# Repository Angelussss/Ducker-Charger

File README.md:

<div align="center">

# ⚡ Ducker-Charger

**A fully custom, open-source smart power bank, designed from scratch.**

*4S3P Li-Ion pack · bidirectional USB-PD · bench-supply output · TFT telemetry UI*

<table>
  <tr>
    <td align="center"></td>
    <td align="center"></td>
  </tr>
  <tr>
    <td align="center"><em>Enclosure (prototype 3, lid off)</em></td>
    <td align="center"><em>Live telemetry UI</em></td>
  </tr>
</table>

</div>

> [!WARNING]
> **Work in progress: the design is not yet validated.** This project involves
> Li-Ion batteries, which can overheat, catch fire, or explode if mishandled.
> Take any information here at your own risk and read the safety note below.

## 🌟 Highlights

* **115 Wh**: 12× 18650 cells (Sony Murata VTC5, 4S3P), 14.4 V nominal / 16.8 V max
* **2× USB-C PD**: primary port is bidirectional (charges the pack *and* powers loads)
* **2× USB-A**: fixed 5 V, individually switchable, current-monitored
* **Lab output**: banana-jack rail that behaves like a bench power supply
* **Hardware-autonomous BMS**: BQ77915 protection works even if all firmware fails
* **STM32F401 supervisor**: power-state FSM, charge management, TFT + rotary-encoder UI
* **On-device gauge calibration**: guided 9-step wizard on the display; a multimeter is the only tool needed (no bqStudio / EV2400)
* **Develop without hardware**: full-PCB emulator, desktop UI simulator, host-side unit tests

## ⚠️ Safety & Disclaimer

* **I assume no liability** for any damage to property, people, or components resulting from the construction or use of this project.
* Always double-check polarity before connecting the batteries.
* Do not attempt to assemble this circuit if you are not experienced in handling lithium batteries.

## 🛠️ Requirements

**Hardware**
* Assembled mainboard + Sensing-Board (`PCB/`)
* 12× 18650 Li-Ion cells, 4S3P (e.g. Sony/Murata VTC5)
* ST-Link V2 (or compatible SWD probe) to flash the STM32F401RBT6
* A USB-PD charger for the primary port, plus USB-C/USB-A cables to exercise the outputs

**Software**
* `arm-none-eabi-gcc`: the firmware builds via the CubeMX-generated `Makefile` in `firmware/cubeMX/`, no IDE required
* `st-flash` (`stlink-tools`) or STM32CubeProgrammer, to flash over SWD
* `gcc` + `SDL2`: only needed for `firmware/emulator/` and `firmware/interface-tester/` (no hardware required to run these)
* Optional: STM32CubeIDE / STM32CubeMX, only to regenerate peripheral init code from `cubeMX.ioc`

## 🧩 Architecture

Distributed design: cell safety, power conversion, PD negotiation and gauging
each live in a dedicated IC; the STM32 supervises, aggregates telemetry and
drives the UI. Block diagram in [`PCB/README.md`](PCB/README.md).

<details>
<summary><strong>Full IC breakdown (10 subsystems)</strong></summary>
<br>

| Subsystem | Part | Role |
|-----------|------|------|
| Safety / Protection | TI **BQ77915** + N-ch MOSFETs | Autonomous, software-independent cell OV/UV/SC/OC cutoff (4S, always-on) |
| Charger | TI **BQ25713** | Buck-boost NVDC battery charger (driven by the TPS25750 on a private I²C bus) |
| Main USB-C PD | TI **TPS25750** | Primary PD port controller; patch bundle streamed by the MCU at every boot |
| Aux USB-C PD | Infineon **CYPD3175** (CCG3PA) | Secondary PD port negotiation (replaced the EOL STUSB4710) |
| Aux programmable rail | ST **STPD01** | I²C-programmable supply for the secondary USB-C / lab output |
| Fuel gauge | TI **BQ34Z100-R2** | Impedance Track™ State-of-Charge / Time-to-Empty |
| Telemetry | TI **INA3221** | 3-channel voltage/current monitoring |
| Step-down | TI **TPS54302 / TPS54202** | Auxiliary rails |
| ESD / I²C isolation | **USBLC6**, **ISO1540** | Port ESD protection, isolated I²C to the battery-referenced gauge |
| Host | **STM32F401RBT6** | I²C master, power-state FSM, thermal manager, HMI / supervisor |

</details>

## 📂 Repository

| Path | Contents |
| --- | --- |
| [`PCB/`](PCB/README.md) | KiCad projects: main board + cell sensing board |
| [`firmware/`](firmware/) | STM32 firmware, PD controller configs, emulator, UI simulator, tests |
| [`docs/`](docs/README.md) | Documentation, start here |
| [`powerbank_enclosure/`](powerbank_enclosure/) | 3D-printable enclosure (F3D, STEP, STL, renders) |

<details>
<summary><strong>Full tree</strong></summary>

```text
Ducker-Charger/
├── PCB/
│   ├── Ducker-Charger/         # Main charger board (schematics, layout, datasheets)
│   └── Sensing-Board/          # Cell sensing board
├── firmware/
│   ├── cubeMX/                 # STM32F401 firmware (FSM, charge mgmt, UI, drivers)
│   ├── TPS25750/               # Primary PD controller config (JSON project + .bin)
│   ├── CYPD3175/               # Secondary PD controller firmware (hex, patches, LED driver)
│   ├── emulator/               # Full-PCB emulator: real firmware vs IC models (SDL)
│   ├── interface-tester/       # Desktop UI simulator (SDL)
│   └── tests/                  # Host-side unit tests (FSM, charge, HPI, math)
├── powerbank_enclosure/        # 3D-printable enclosure (F3D, STEP, STL, renders)
└── docs/
    ├── hardware/               # Power architecture, pin map / BSP reference
    ├── firmware/               # Architecture, FSM, charge mgmt, boot, UI
    └── assets/                 # UI demo gif
```

</details>

## 📖 Documentation

Start from **[`docs/README.md`](docs/README.md)**: full system overview and a
walkthrough of how the firmware works, with links to:

* [Hardware architecture](docs/hardware/Hardware_Architecture.md) · [pin-level BSP reference](docs/hardware/BSP_reference.md)
* [Firmware architecture](docs/firmware/Firmware_Architecture.md) · [power-state FSM](docs/firmware/FSM.md) · [charge management](docs/firmware/Charge_Management.md)
* [Boot & IC provisioning](docs/firmware/Boot_and_Provisioning.md) · [gauge calibration wizard](docs/firmware/Gauge_Calibration.md) · [UI / display reference](docs/firmware/UI_and_Display.md)
* [KiCad projects & block diagram](PCB/README.md)

## 🎮 User Guide

Boots to **MAIN** (battery %, voltage/current, live current graph). Rotate the
encoder to cycle **MAIN → DETAILS → GRAPH → PORTS → STATS**; press to open
**SETTINGS** (per-port toggles, Lab output voltage/current, USB-C2 output
ceiling, lock-all, brightness/auto-sleep, gauge calibration wizard, shutdown).
A long press (or SETTINGS → Shutdown) puts the device into deep sleep; a
short press wakes it back up if a charger is attached. Fault conditions open a
dedicated FAULT screen automatically, naming the cause.

Full screen-by-screen reference: [`docs/firmware/UI_and_Display.md`](docs/firmware/UI_and_Display.md).

## 🎥 Presentation & Demo

* 📊 Slides: [Google Slides](https://docs.google.com/presentation/d/1OwDXiBUUQ08QPd7Jknc45msrt9zxNyJMcGTFnEZxmk4/edit?usp=sharing)
* 🎬 YouTube walkthrough: [youtu.be/msm0JCK7GhI](https://youtu.be/msm0JCK7GhI)

## 👥 Team & Contributions

The project is split by layer, one owner per layer end-to-end (design, implementation, docs, tests):

| Member | Layer owned |
|---|---|
| Angelo Perotti | Hardware (PCB/KiCad), CubeMX project bring-up, boot & IC provisioning |
| Francesco Brunelli | Charge management: sensors, actuators, fault detection |
| Michelangelo Calia | Power-state FSM & fault handling |
| Maya | Display/UI stack: driver, widgets, screens, navigation |

## 🤝 Contributing

Issues, suggestions, and pull requests are momentarily suspended, as this is a university course project.

## 📜 License

Released under the [Creative Commons Attribution-NonCommercial 4.0 Internationalç
License (CC BY-NC 4.0)](LICENSE). © 2026 Angelo Perotti.

You are free to use, modify, and build upon this work for **non-commercial**
purposes, as long as you **credit the author**. See [NOTICE](NOTICE) for
attribution details.

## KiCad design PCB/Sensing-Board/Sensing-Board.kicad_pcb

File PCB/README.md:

# PCB: KiCad Projects

Two KiCad projects make up the Ducker-Charger hardware:

| Project | Contents |
| --- | --- |
| `Ducker-Charger/` | Main charger board: schematics, PCB layout, production files |
| `Sensing-Board/` | Cell sensing board (tap connections from the 4S pack to the BMS) |

## Main board schematic structure

| Sheet | File | Contents |
| --- | --- | --- |
| Root | `Ducker-Charger.kicad_sch` | Top level, sheet interconnections |
| High power | `high_pow.kicad_sch` | TPS25750 (primary USB-C PD), BQ25713 buck-boost charger, VBUS power path |
| Low power | `low_pow.kicad_sch` | CYPD3175 (secondary USB-C PD), STPD01 programmable rail, USB-A load switches, INA3221 sensing, lab-output switching |
| Logic | `Logic.kicad_sch` | STM32F401RBT6, display/encoder interface, logic supply |
| BMS | `BMS.kicad_sch` | BQ77915 protection, BQ34Z100-R2 fuel gauge, ISO1540 I2C isolator, protection FETs |

> The secondary PD controller is the Infineon **CYPD3175**: it replaced the
> ST **STUSB4710** (EOL).

Component datasheets and technical reference manuals used during the design are
collected in [`Ducker-Charger/docs/`](Ducker-Charger/docs/).

## System block diagram

```mermaid
flowchart TB
    subgraph BMS["BMS (always-on hardware safety)"]
        PACK["4S3P Sony VTC5<br/>14.4V nom / 16.8V max"]
        BQ77915["BQ77915 protector<br/>+ N-ch FETs (low-side)"]
        GAUGE["BQ34Z100-R2 fuel gauge<br/>(battery-referenced)"]
        PACK --> BQ77915
        PACK -.->|sense| GAUGE
    end

    subgraph HP["High-power stage"]
        TPS["TPS25750<br/>primary USB-C PD"]
        BQ25713["BQ25713<br/>buck-boost NVDC charger"]
        USBC1(("USB-C1<br/>bidirectional PD"))
        USBC1 <--> TPS
        TPS <-->|private I2C_EX| BQ25713
    end

    subgraph LP["Low-power / aux stage"]
        CYPD["CYPD3175<br/>secondary USB-C PD"]
        STPD01["STPD01<br/>programmable rail"]
        USBC2(("USB-C2<br/>source-only"))
        USBA(("2x USB-A<br/>5V"))
        LAB(("Lab output"))
        INA["INA3221<br/>current monitor"]
        CYPD <--> USBC2
        STPD01 --> USBC2
        STPD01 --> LAB
        INA --- USBA
    end

    subgraph LOGIC["Logic"]
        MCU["STM32F401RBT6"]
        DISP["ILI9341 TFT (SPI1)"]
        ENC["Rotary encoder (TIM3)"]
        MCU --> DISP
        ENC --> MCU
    end

    BQ77915 -->|+BATT| BQ25713
    BQ25713 -->|VSYS| LP
    BQ25713 -->|VSYS| LOGIC

    MCU <-->|"I2C3 (PD bus)"| TPS
    MCU <-->|"I2C1 (system bus, HPI)"| CYPD
    MCU <-->|I2C1| STPD01
    MCU <-->|I2C1| INA
    MCU <-->|"I2C1 via ISO1540"| GAUGE
```

Bus-level detail (pins, addresses):
[`docs/hardware/BSP_reference.md`](../docs/hardware/BSP_reference.md).

## Production

`*/production/` holds the fabrication outputs (gerber zip + IPC netlist)
generated with the JLCPCB fabrication toolkit. Regenerate after any layout
change; do not hand-edit.

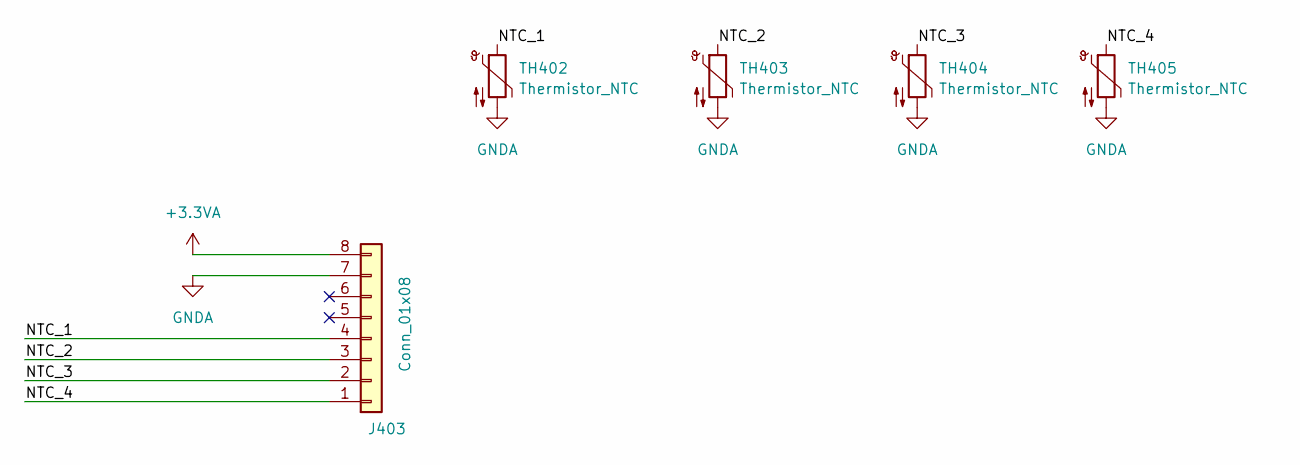
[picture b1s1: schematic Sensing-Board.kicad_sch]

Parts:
J403: Conn_01x08; Molex_200528-0080_1x08-1MP_P1.00mm_Horizontal
TH402, TH403, TH404, TH405: Thermistor_NTC; R_0603_1608Metric

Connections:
+3.3VA: J403.8
/NTC_1: J403.4, TH402.1
/NTC_2: J403.3, TH403.1
/NTC_3: J403.2, TH404.1
/NTC_4: J403.1, TH405.1
GNDA: J403.7, TH402.2, TH403.2, TH404.2, TH405.2

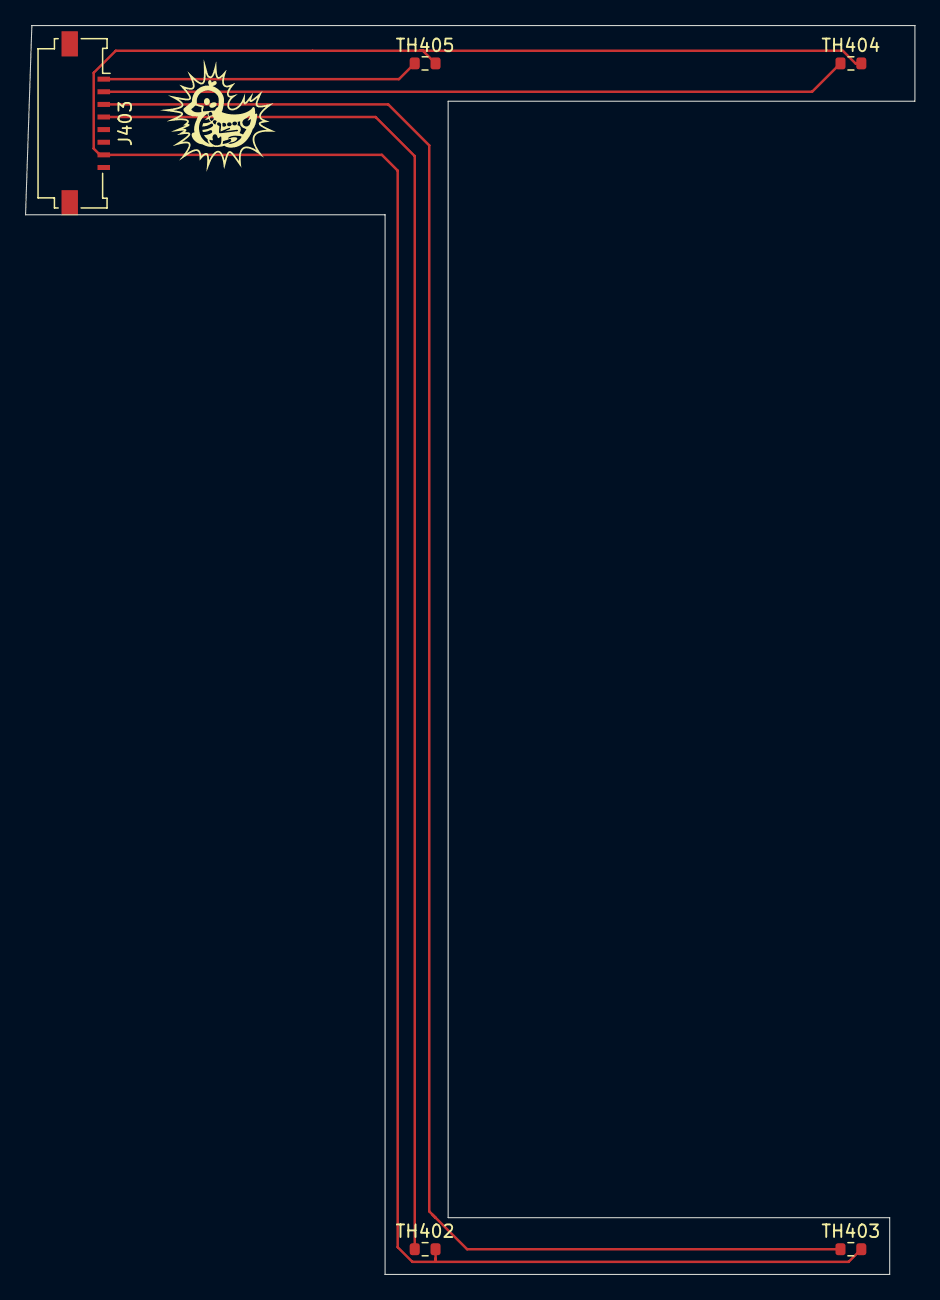
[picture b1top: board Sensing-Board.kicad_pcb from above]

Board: 2 copper layers, 70.5 x 99.0 mm, 6 parts (1 on the bottom side), 5 nets.

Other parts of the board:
kibuzzard-6A3C49BF: G***; kibuzzard-6A3C49BF

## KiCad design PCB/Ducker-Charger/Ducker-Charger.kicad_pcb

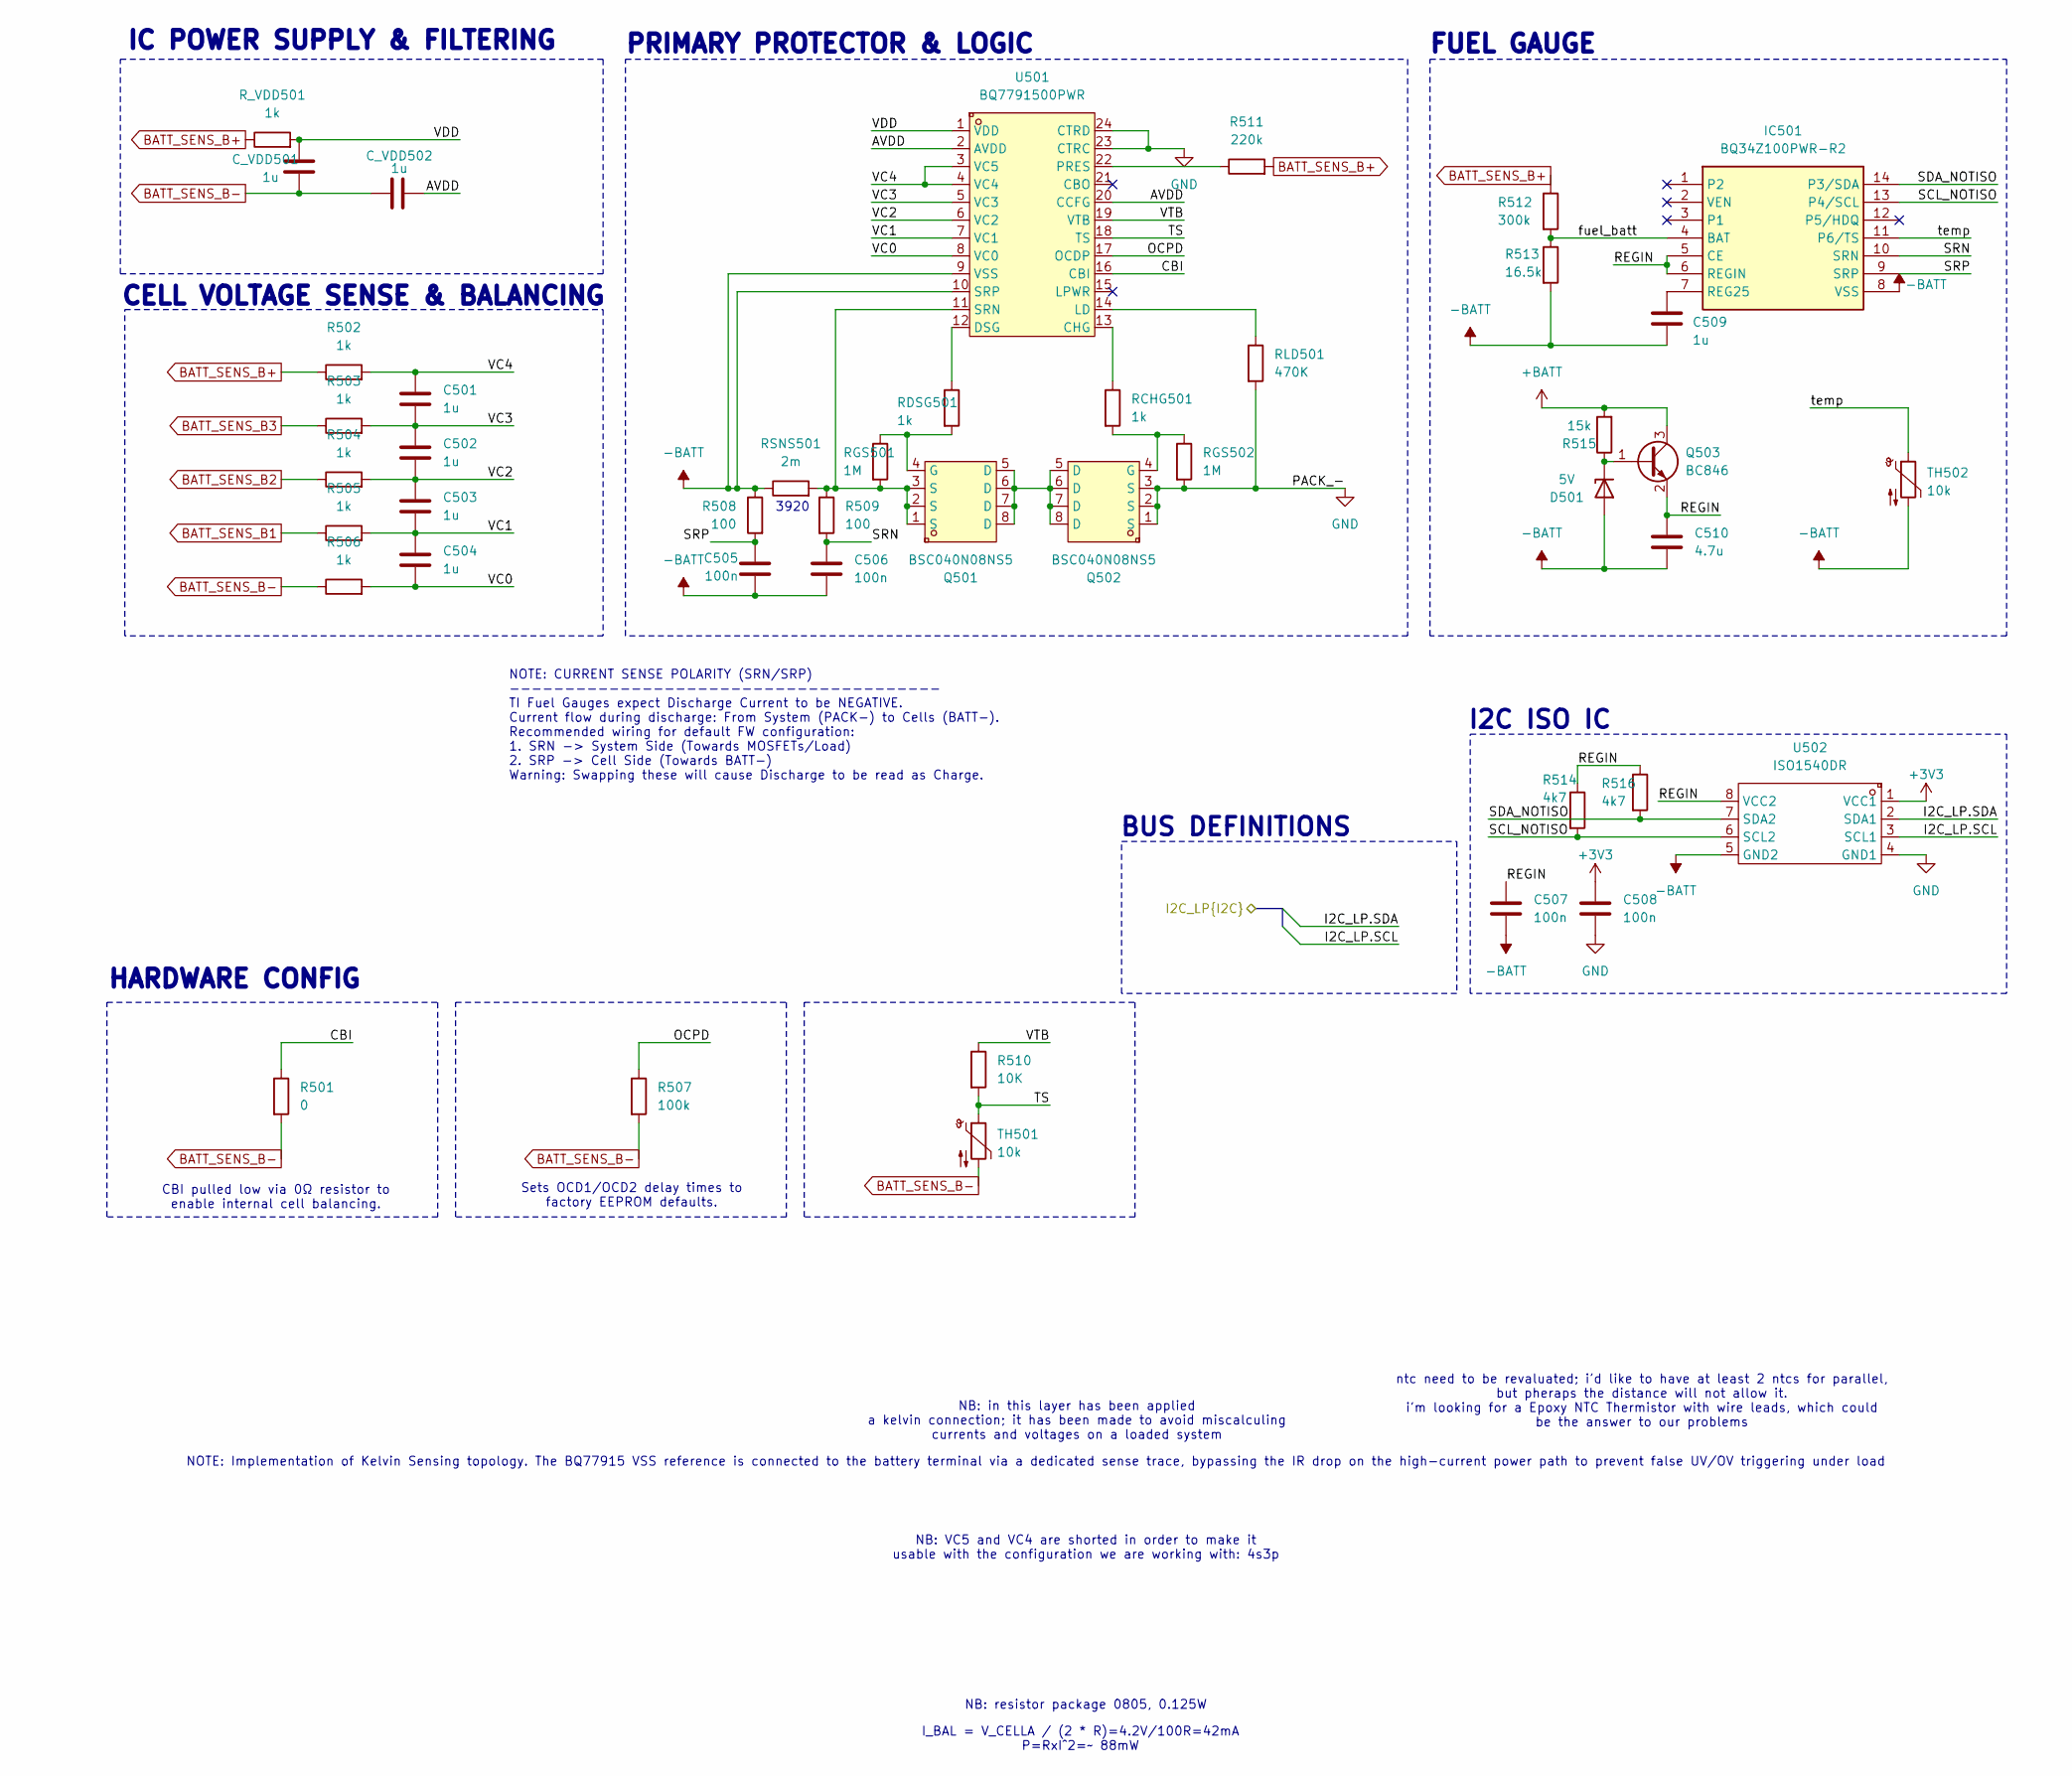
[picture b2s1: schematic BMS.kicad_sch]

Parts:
C501, C502, C503, C504, C509: 1u; C_0805_2012Metric
C505, C506, C507, C508: 100n; C_0603_1608Metric
C510: 4.7u; C_0805_2012Metric
C_VDD501, C_VDD502: 1u; C_0805_2012Metric
D501: 5V; D_SOD-123
IC501: BQ34Z100PWR-R2; SOP65P640X120-14N; Mouser Part Number 595-BQ34Z100PWR-R2
Q501, Q502: BSC040N08NS5; PG-TDSON-8_L5.9-W5.1-P1.27-LS6.2-BL; LCSC Part C534333
Q503: BC846; SOT-23
R501: 0; R_0603_1608Metric
R502, R503, R504, R505, R506: 1k; R_0603_1608Metric
R507: 100k; R_0603_1608Metric
R508, R509: 100; R_0603_1608Metric
R510: 10K; R_0603_1608Metric
R511: 220k; R_0603_1608Metric
R512: 300k; R_0603_1608Metric
R513: 16.5k; R_0603_1608Metric
R514, R516: 4k7; R_0603_1608Metric
R515: 15k; R_0603_1608Metric
RCHG501: 1k; R_0603_1608Metric
RDSG501: 1k; R_0603_1608Metric
RGS501, RGS502: 1M; R_0603_1608Metric
RLD501: 470K; R_0603_1608Metric
RSNS501: 2m; R3920; lcsc name Milliohm HoJLR2512-3W-5mR-1%
R_VDD501: 1k; R_0603_1608Metric
TH501, TH502: 10k; R_0603_1608Metric
U501: BQ7791500PWR; TSSOP-24_L7.8-W4.4-P0.65-LS6.4-BL; LCSC Part C2876946
U502: ISO1540DR; SOIC-8_L4.9-W3.9-P1.27-LS6.0-BL; LCSC Part C179739

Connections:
+3V3: C508.1, U502.1 (VCC1); also elsewhere on the board
+BATT: Q503.3 (C), R515.2; also elsewhere on the board
-BATT: C505.2, C506.2, C507.2, C509.2, C510.2, D501.2 (A), IC501.8 (VSS), R508.1, R513.2, RSNS501.1, TH502.2, U501.9 (VSS), U501.10 (SRP), U502.5 (GND2); also elsewhere on the board
/BMS/AVDD: C_VDD502.2, U501.2 (AVDD), U501.20 (CCFG)
/BMS/CBI: R501.1, U501.16 (CBI)
/BMS/I2C_LP.SCL: U502.3 (SCL1); also elsewhere on the board
/BMS/I2C_LP.SDA: U502.2 (SDA1); also elsewhere on the board
/BMS/OCPD: R507.1, U501.17 (OCDP)
/BMS/REGIN: C507.1, C510.1, IC501.5 (CE), IC501.6 (REGIN), Q503.2 (E), R514.1, R516.1, U502.8 (VCC2)
/BMS/SCL_NOTISO: IC501.13 (P4/SCL), R514.2, U502.6 (SCL2)
/BMS/SDA_NOTISO: IC501.14 (P3/SDA), R516.2, U502.7 (SDA2)
/BMS/SRN: C506.1, IC501.10 (SRN), R509.2
/BMS/SRP: C505.1, IC501.9 (SRP), R508.2
/BMS/TS: R510.2, TH501.1, U501.18 (TS)
/BMS/VC0: C504.2, R506.2, U501.8 (VC0)
/BMS/VC1: C503.2, C504.1, R505.2, U501.7 (VC1)
/BMS/VC2: C502.2, C503.1, R504.2, U501.6 (VC2)
/BMS/VC3: C501.2, C502.1, R503.2, U501.5 (VC3)
/BMS/VC4: C501.1, R502.2, U501.3 (VC5), U501.4 (VC4)
/BMS/VDD: C_VDD501.1, R_VDD501.2, U501.1 (VDD)
/BMS/VTB: R510.1, U501.19 (VTB)
/BMS/fuel_batt: IC501.4 (BAT), R512.2, R513.1
/BMS/temp: IC501.11 (P6/TS), TH502.1
BATT_SENS_B1: R505.1; also elsewhere on the board
BATT_SENS_B2: R504.1; also elsewhere on the board
BATT_SENS_B3: R503.1; also elsewhere on the board
BATT_SENS_B+: R502.1, R511.2, R512.1, R_VDD501.1; also elsewhere on the board
BATT_SENS_B-: C_VDD501.2, C_VDD502.1, R501.2, R506.1, R507.2, TH501.2; also elsewhere on the board
GND: C508.2, Q502.1 (S), Q502.2 (S), Q502.3 (S), RGS502.2, RLD501.2, U501.23 (CTRC), U501.24 (CTRD), U502.4 (GND1); also elsewhere on the board
unnamed: D501.1 (K), Q503.1 (B), R515.1
unnamed: C509.1, IC501.7 (REG25)
unnamed: Q501.5 (D), Q501.6 (D), Q501.7 (D), Q501.8 (D), Q502.5 (D), Q502.6 (D), Q502.7 (D), Q502.8 (D)
unnamed: Q501.4 (G), RDSG501.2, RGS501.1
unnamed: Q502.4 (G), RCHG501.2, RGS502.1
unnamed: RCHG501.1, U501.13 (CHG)
unnamed: RDSG501.1, U501.12 (DSG)
unnamed: RLD501.1, U501.14 (LD)
unnamed: R511.1, U501.22 (PRES)
unnamed: Q501.1 (S), Q501.2 (S), Q501.3 (S), R509.1, RGS501.2, RSNS501.2, U501.11 (SRN)

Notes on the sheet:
NB: resistor package 0805, 0.125W
I2C ISO IC
NOTE: Implementation of Kelvin Sensing topology. The BQ77915 VSS reference is connected to the battery terminal via a dedicated sense trace, bypassing the IR drop on the high-current power path to prevent false UV/OV triggering under load
FUEL GAUGE
I_BAL = V_CELLA / (2 * R)=4.2V/100R=42mA P=RxI^2=~ 88mW
NOTE: CURRENT SENSE POLARITY (SRN/SRP) --------------------------------------- TI Fuel Gauges expect Discharge Current to be NEGATIVE. Current flow during discharge: From System (PACK-) to Cells (BATT-). Recommended wiring for default FW configuration: 1. SRN -> System Side (Towards MOSFETs/Load) 2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
IC POWER SUPPLY & FILTERING
ntc need to be revaluated; i'd like to have at least 2 ntcs for parallel, but pheraps the distance will not allow it. i'm looking for a Epoxy NTC Thermistor with wire leads, which could be the answer to our problems
NB: in this layer has been applied a kelvin connection; it has been made to avoid miscalculing currents and voltages on a loaded system
Sets OCD1/OCD2 delay times to factory EEPROM defaults.
HARDWARE CONFIG
CELL VOLTAGE SENSE & BALANCING
BUS DEFINITIONS
NB: VC5 and VC4 are shorted in order to make it usable with the configuration we are working with: 4s3p
3920
CBI pulled low via 0Ω resistor to enable internal cell balancing.
PRIMARY PROTECTOR & LOGIC

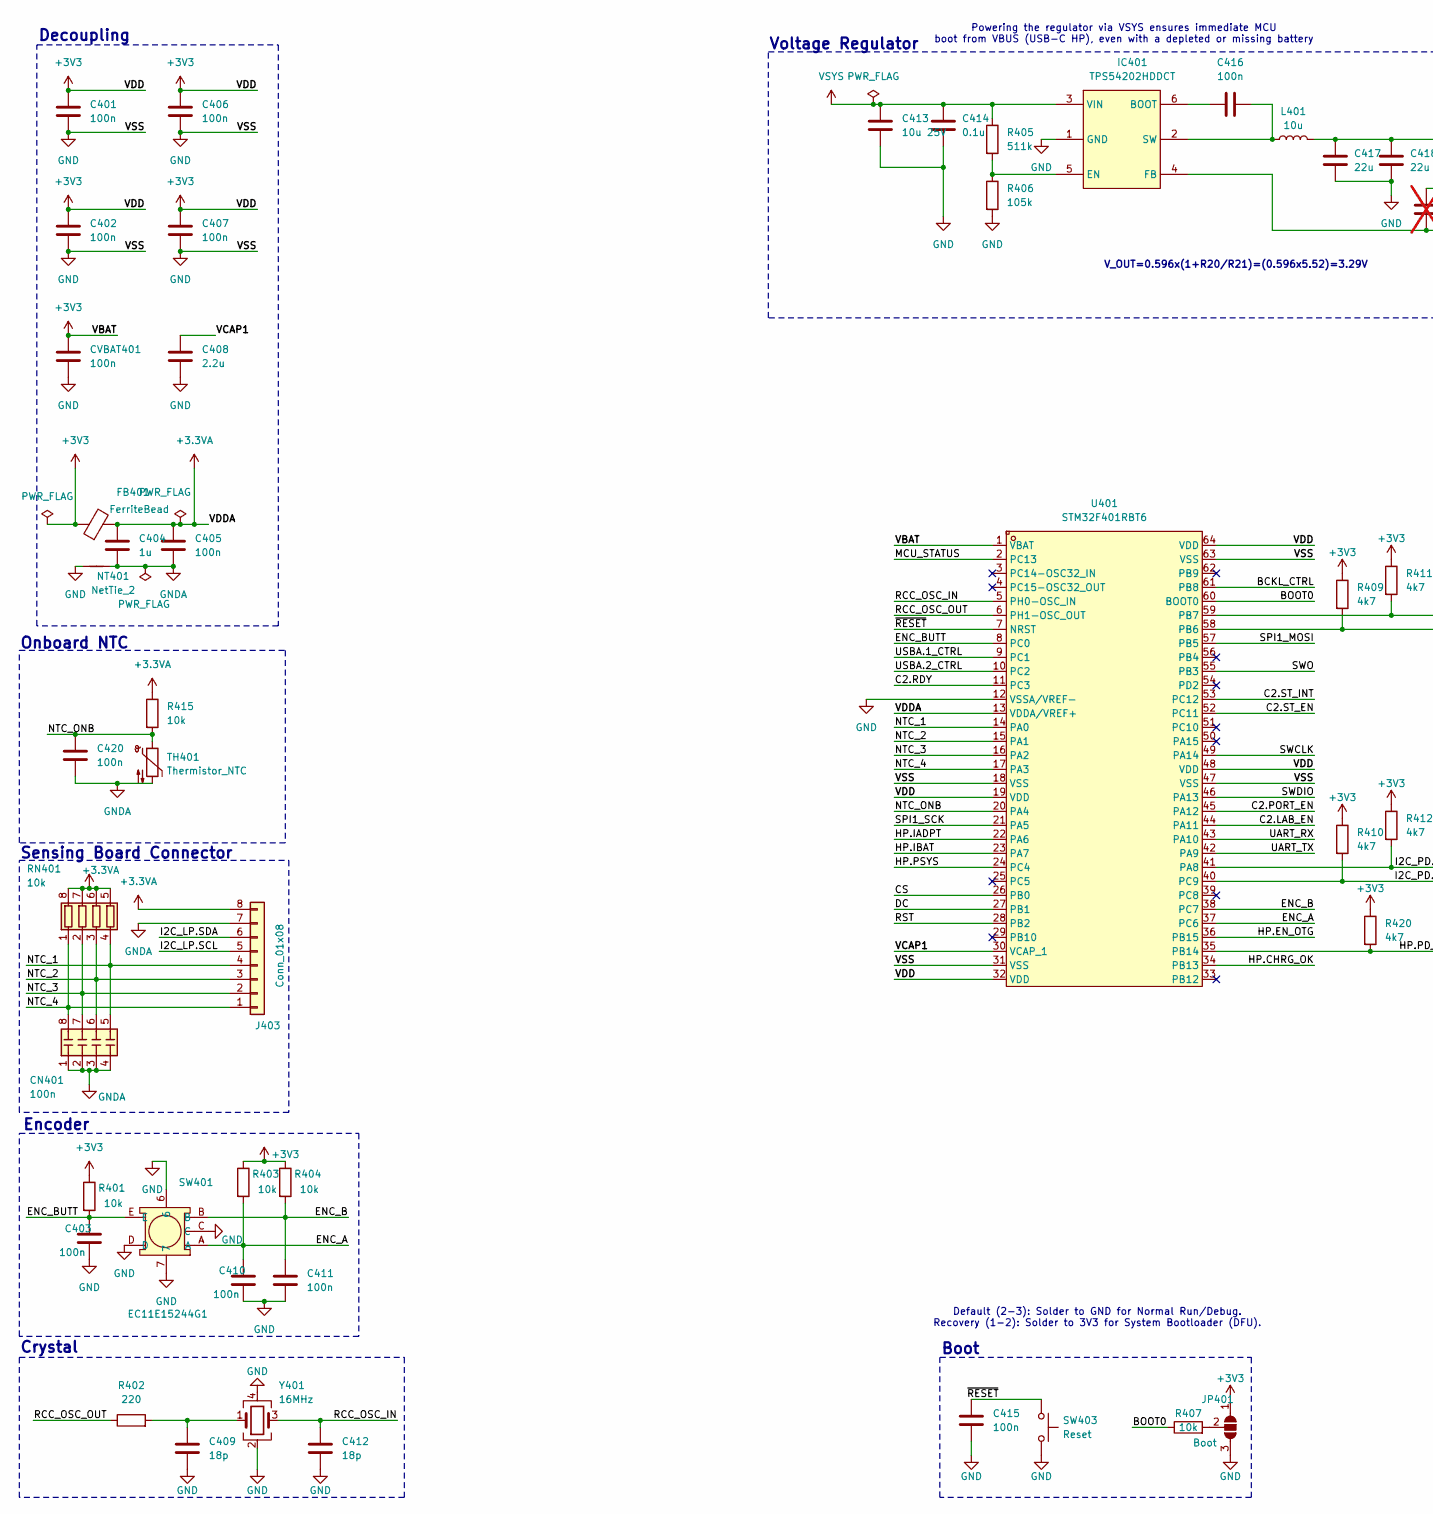
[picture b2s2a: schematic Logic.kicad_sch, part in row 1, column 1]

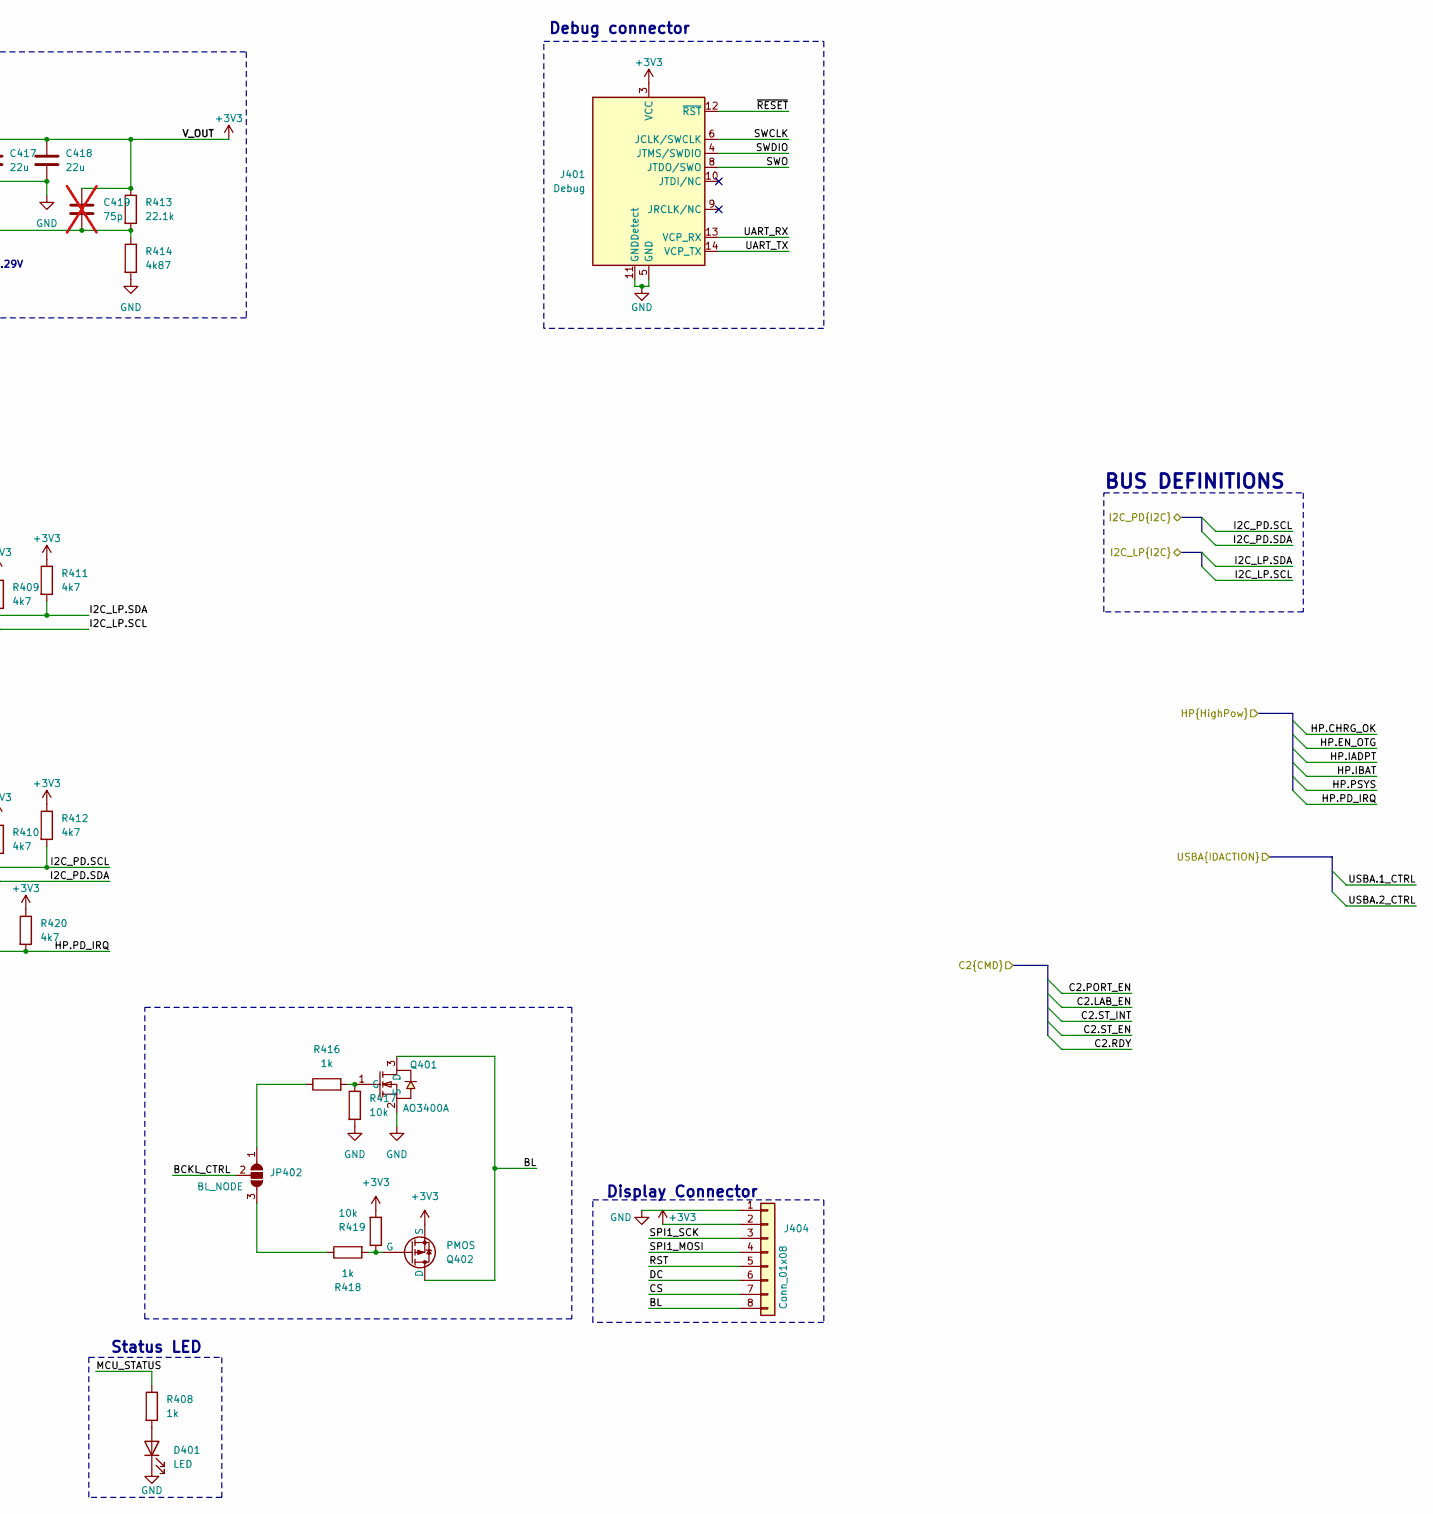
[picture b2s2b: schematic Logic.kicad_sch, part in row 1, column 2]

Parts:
C401, C402, C403, C405, C406, C407, C410, C411, C415, C420: 100n; C_0603_1608Metric
C404: 1u; C_0805_2012Metric
C408: 2.2u; C_0805_2012Metric
C409, C412: 18p; C_0603_1608Metric
C413: 10u 25V; C_1206_3216Metric
C414: 0.1u; C_0805_2012Metric
C416: 100n; C_0805_2012Metric
C417, C418: 22u; C_0805_2012Metric
C419: 75p; C_0805_2012Metric; not fitted
CN401: 100n; R_Array_Concave_4x0603
CVBAT401: 100n; R_0603_1608Metric
D401: LED; LED_0603_1608Metric
FB401: FerriteBead; L_0603_1608Metric
IC401: TPS54202HDDCT; SOT95P280X110-6N; Mouser Part Number 595-TPS54202HDDCT
J401: Debug; SAMTEC_FTSH-107-01-L-DV-K-TR
J403: Conn_01x08; Molex_200528-0080_1x08-1MP_P1.00mm_Horizontal
J404: Conn_01x08; JST_EH_B8B-EH-A_1x08_P2.50mm_Vertical
JP401: Boot; SolderJumper-3_P1.3mm_Open_RoundedPad1.0x1.5mm
JP402: BL_NODE; SolderJumper-3_P1.3mm_Open_RoundedPad1.0x1.5mm
L401: 10u; L_6.3x6.3_H3
NT401: NetTie_2; NetTie-2_SMD_Pad0.5mm
Q401: AO3400A; SOT-23-3_L2.9-W1.3-P1.90-LS2.4-BR; LCSC Part C20917
Q402: PMOS; SOT-23-3_L2.9-W1.3-P1.90-LS2.4-BR
R401, R403, R404, R407, R415, R417, R419: 10k; R_0603_1608Metric
R402: 220; R_0603_1608Metric
R405: 511k; R_0603_1608Metric
R406: 105k; R_0603_1608Metric
R408, R416, R418: 1k; R_0603_1608Metric
R409, R410, R411, R412, R420: 4k7; R_0603_1608Metric
R413: 22.1k; R_0603_1608Metric
R414: 4k87; R_0603_1608Metric
RN401: 10k; R_Array_Convex_4x0603
SW401: EC11E15244G1; SW-TH_EC11E15244G1; LCSC Part C370970
SW403: Reset; SW_SPST_FSMSM
TH401: Thermistor_NTC; R_0603_1608Metric
U401: STM32F401RBT6; LQFP-64_L10.0-W10.0-P0.50-LS12.0-BL; LCSC Part C75278
Y401: 16MHz; Crystal_SMD_EuroQuartz_MT-4Pin_3.2x2.5mm

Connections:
+3.3VA: C404.1, C405.1, FB401.2, J403.8, R415.1, RN401.5 (R4.2), RN401.6 (R3.2), RN401.7 (R2.2), RN401.8 (R1.2), U401.13 (VDDA/VREF+)
+3V3: C401.1, C402.1, C406.1, C407.1, C417.1, C418.1, C419.2, CVBAT401.1, FB401.1, J401.3 (VCC), J404.2, JP401.1 (A), L401.2, Q402.3 (S), R401.1, R403.1, R404.1, R409.1, R410.1, R411.1, R412.1, R413.1, R419.2, R420.1, U401.1 (VBAT), U401.19 (VDD), U401.32 (VDD), U401.48 (VDD), U401.64 (VDD); also elsewhere on the board
/BMS/I2C_LP.SCL: J403.5, R409.2, U401.58 (PB6); also elsewhere on the board
/BMS/I2C_LP.SDA: J403.6, R411.2, U401.59 (PB7); also elsewhere on the board
/High_pow/HP.CHRG_OK: U401.34 (PB13); also elsewhere on the board
/High_pow/HP.EN_OTG: U401.36 (PB15); also elsewhere on the board
/High_pow/HP.IADPT: U401.22 (PA6); also elsewhere on the board
/High_pow/HP.IBAT: U401.23 (PA7); also elsewhere on the board
/High_pow/HP.PD_IRQ: R420.2, U401.35 (PB14); also elsewhere on the board
/High_pow/HP.PSYS: U401.24 (PC4); also elsewhere on the board
/High_pow/I2C_PD.SCL: R412.2, U401.41 (PA8); also elsewhere on the board
/High_pow/I2C_PD.SDA: R410.2, U401.40 (PC9); also elsewhere on the board
/Logic/BCKL_CTRL: JP402.2 (C), U401.61 (PB8)
/Logic/BL: J404.8, Q401.3 (D), Q402.1 (D)
/Logic/BOOT0: R407.1, U401.60 (BOOT0)
/Logic/C2.LAB_EN: U401.44 (PA11); also elsewhere on the board
/Logic/C2.PORT_EN: U401.45 (PA12); also elsewhere on the board
/Logic/C2.RDY: U401.11 (PC3); also elsewhere on the board
/Logic/C2.ST_EN: U401.52 (PC11); also elsewhere on the board
/Logic/C2.ST_INT: U401.53 (PC12); also elsewhere on the board
/Logic/CS: J404.7, U401.26 (PB0)
/Logic/DC: J404.6, U401.27 (PB1)
/Logic/ENC_A: C410.1, R403.2, SW401.A, U401.37 (PC6)
/Logic/ENC_B: C411.1, R404.2, SW401.B, U401.38 (PC7)
/Logic/ENC_BUTT: C403.1, R401.2, SW401.E, U401.8 (PC0)
/Logic/MCU_STATUS: R408.1, U401.2 (PC13)
/Logic/NTC_1: CN401.5 (R4.2), J403.4, RN401.4 (R4.1), U401.14 (PA0)
/Logic/NTC_2: CN401.6 (R3.2), J403.3, RN401.3 (R3.1), U401.15 (PA1)
/Logic/NTC_3: CN401.7 (R2.2), J403.2, RN401.2 (R2.1), U401.16 (PA2)
/Logic/NTC_4: CN401.8 (R1.2), J403.1, RN401.1 (R1.1), U401.17 (PA3)
/Logic/NTC_ONB: C420.1, R415.2, TH401.1, U401.20 (PA4)
/Logic/RCC_OSC_IN: C412.1, U401.5 (PH0-OSC_IN), Y401.3
/Logic/RCC_OSC_OUT: R402.1, U401.6 (PH1-OSC_OUT)
/Logic/RST: J404.5, U401.28 (PB2)
/Logic/SPI1_MOSI: J404.4, U401.57 (PB5)
/Logic/SPI1_SCK: J404.3, U401.21 (PA5)
/Logic/SWCLK: J401.6 (JCLK/SWCLK), U401.49 (PA14)
/Logic/SWDIO: J401.4 (JTMS/SWDIO), U401.46 (PA13)
/Logic/SWO: J401.8 (JTDO/SWO), U401.55 (PB3)
/Logic/UART_RX: J401.13 (VCP_RX), U401.43 (PA10)
/Logic/UART_TX: J401.14 (VCP_TX), U401.42 (PA9)
/Logic/USBA.1_CTRL: U401.9 (PC1); also elsewhere on the board
/Logic/USBA.2_CTRL: U401.10 (PC2); also elsewhere on the board
/Logic/VCAP1: C408.1, U401.30 (VCAP_1)
/Logic/~RESET: C415.1, J401.12 (~RST), SW403.1, U401.7 (NRST)
GND: C401.2, C402.2, C403.2, C406.2, C407.2, C408.2, C409.2, C410.2, C411.2, C412.2, C413.2, C414.2, C415.2, C417.2, C418.2, CVBAT401.2, D401.1 (K), IC401.1 (GND), J401.5 (GND), J401.7 (GND), J401.11 (GNDDetect), J404.1, JP401.3 (B), NT401.1, Q401.2 (S), R406.2, R414.2, R417.2, SW401.6, SW401.7, SW401.C, SW401.D, SW403.2, U401.12 (VSSA/VREF-), U401.18 (VSS), U401.31 (VSS), U401.47 (VSS), U401.63 (VSS), Y401.2, Y401.4; also elsewhere on the board
GNDA: C404.2, C405.2, C420.2, CN401.1 (R1.1), CN401.2 (R2.1), CN401.3 (R3.1), CN401.4 (R4.1), J403.7, NT401.2, TH401.2
unnamed: C409.1, R402.2, Y401.1
unnamed: D401.2 (A), R408.2
unnamed: C416.1, IC401.6 (BOOT)
unnamed: IC401.5 (EN), R405.2, R406.1
unnamed: C419.1, IC401.4 (FB), R413.2, R414.1
unnamed: C416.2, IC401.2 (SW), L401.1
unnamed: JP401.2 (C), R407.2
unnamed: JP402.1 (A), R416.1
unnamed: JP402.3 (B), R418.1
unnamed: Q401.1 (G), R416.2, R417.1
unnamed: Q402.2 (G), R418.2, R419.1
VSYS: C413.1, C414.1, IC401.3 (VIN), R405.1; also elsewhere on the board

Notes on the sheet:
Status LED
Crystal
Boot
V_OUT=0.596x(1+R20/R21)=(0.596x5.52)=3.29V
Sensing Board Connector
Onboard NTC
Voltage Regulator
Encoder
Debug connector
Powering the regulator via VSYS ensures immediate MCU boot from VBUS (USB-C HP), even with a depleted or missing battery
BUS DEFINITIONS
Default (2-3): Solder to GND for Normal Run/Debug. Recovery (1-2): Solder to 3V3 for System Bootloader (DFU).
Decoupling
Display Connector

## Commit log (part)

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2025-09-30 feat: added explanation of what the base idea is
2025-10-14 feat: added kicad project
2025-11-17 feat: general layout
2025-11-17 fix: typo
2025-11-17 feat: added High power main sections
2025-11-18 feat: added capacitors to BUCK-BOOST POWER STAGE
2025-11-18 feat: completed High power stage
2025-11-18 fix: unconnected pins, wrong connections
2025-11-18 feat: begun Logic
2025-11-19 fix: placement
2025-11-20 feat: added CUBE-MX project
2025-11-25 fix: CUBE-MX project placement and name
2025-11-25 fix: removed useless files
2025-11-25 fix: changed cell sensing connector
2025-11-25 feat: started BMS configuration
2025-11-26 feat: started CHG and DSG in BMS
2025-11-30 feat: implement basic BQ77915 protection circuit
2025-11-30 feat: added circuit diagram explanation
2025-11-30 fix: syntax error
2025-11-30 feat: initial CubeMX configuration (Clocks, SPI1, I2C1, TIM2)
2025-11-30 feat: progressed MCU setup, completed 3V3 voltage regulator
2025-11-30 feat: added voltage regulator lib and datasheet
2025-11-30 fix: backups and autosaved files
2025-11-30 feat: added BQ34Z100PWR-R2
2025-11-30 fix: placement and values
2025-11-30 fix: autosave e backup
2025-11-30 feat: added debug, ntc sensing and minor fixes
2025-12-01 fix: removed old logic doc as it was outdated
2025-12-02 fix: removed ghost files
2025-12-08 feat: STPD01 setup
2025-12-08 fix: updated project libs
2025-12-08 fix: backups
2025-12-08 feat: added stpd01 datasheet
2025-12-08 fix: minor files
2025-12-12 feat: added stusb4710 datasheet
2025-12-13 feat: substituted IP5389 with BQ25713 + TPS25750
2025-12-13 feat: added STUSB4710AQ1TR
2025-12-13 fix: libs
2025-12-14 feat: completed BQ25713 + TPS25750 config
2025-12-14 feat: added BQ25713 & TPS25750 datasheets
2025-12-14 feat: completed low power sheet
2025-12-14 feat: completed BMS sheet
2025-12-14 feat: added pullup resistors for i2c
2025-12-16 fix: updated README
2025-12-22 feat: progressed overall schematic
2025-12-22 fix: README
    Updated interface details in the README.
2025-12-23 fix: power symbols
2025-12-23 feat: added gitignore
2025-12-23 fix: libs placement
2025-12-23 fix: I2C is now a BUS, no longer a global label
2025-12-23 fix: readability of Buck-Boost power stage
2025-12-23 fix: replaced Schottky Diode sym
2025-12-23 fix: updated gitignore
2025-12-26 fix: MOSFET
2025-12-26 fix: Rshunt
2025-12-26 feat: added I2C iso IC
2025-12-27 fix: short circuited D+ and D- to unlock 3A in usbA
2025-12-27 feat: updated libs
2025-12-27 fix: minor fixes
2025-12-27 feat: added fuse blade
2025-12-27 feat: updated footprints
2025-12-27 feat: completed BMS section
2025-12-27 fix: changed rshunt footprint
2025-12-27 feat: progressed pcb
2025-12-27 fix: completed MCU config
2025-12-27 fix: updated config based on CubeMX
2025-12-28 fix: added missing connections
2025-12-28 feat: PCB v1.0 is now ready
2025-12-28 feat: added gerber files
2025-12-28 fix: removed 90deg tracks
2025-12-28 feat: added sensing board project
2025-12-29 fix: downsized the numbers of load bearing VIAs
2025-12-29 fix: new BUCK-BOOST power stage
2025-12-30 feat: added TPS25750DRJKR datasheet
2025-12-30 fix: removed old High Power section
2025-12-30 fix: remade entire ICs configuration
2025-12-31 fix: MCU connections
2025-12-31 fix: missing files
2026-01-03 feat: fsm general implementation
2026-01-04 feat: added BSP reference docs
2026-01-04 feat: added Hardware_Architecture docs
2026-01-05 fix; Clean up formatting in README.md
2026-01-05 fix: docs placement for BSP
2026-01-05 fix: docs placement for HW architecture
2026-03-02 feat: generated first version of base code from cubeMX
2026-06-08 feat: generated CUBEMX code
2026-06-08 feat: splitted analog line
2026-06-11 Updated gitignore
2026-06-11 feat: Initial commit of charge management system files
2026-06-11 fix: switched to C
2026-06-11 feat: Implemented sensor reading function via ADC
2026-06-12 Updated PCB docs, added BQ34Z100-R2 Technical Reference Manual
2026-06-12 feat: Added FuelGauge sensor reading and GPIO R/W for interrupts and ports enabling
2026-06-12 fix: configuration & parity errors
2026-06-12 feat: regenerated cubeMX files
2026-06-12 feat: added register map
2026-06-13 Feat: minor changes
2026-06-13 feat: Added INA3221 datasheet and TPS25750 Reference Manual
2026-06-13 fix: fixed race conditions by switching I2C fuel gauge sensors readings from non-blocking to blocking
2026-06-13 feat: add UI module headers
    Add include directories for app, display and ui modules.
    Headers define the full architecture: telemetry polling (BQ34Z100 + BQ25713), rotary encoder (TIM3 encoder mode), ILI9341 SPI display driver, GFX primitives, widgets, screens and UI state machine.
    No source files yet - headers only, compile-tested in STM32CubeIDE.
2026-06-14 feat: Added fetch of PD contract and interrupt handling for primary USB-C connection/disconnection
2026-06-16 feat: add ILI9341 display driver and GFX primitives
    ili9341.c: SPI low-level driver for ILI9341/ST7789 TFT display.
    gfx.c: geometry and text primitives built on top of the display driver.
2026-06-16 feat: Added connection/disconnection procedure for the secondary USB-C
2026-06-16 fixed comments and addes features (add telemetry polling and rotary encoder driver)
2026-06-17 fix: fixed adc sensor reading and added get functions for easy data fetch
2026-06-18 fix: code cleanup + fixed temperature conversion for NTC thermistors
2026-06-18 fix: moved charge-management doc file into docs/
2026-06-18 feat: add UI widgets, screens and navigation state machine. integrate UI into main loop
2026-06-19 documentazione display
2026-06-20 feat: added datasheets
2026-06-20 feat: updated gitignore
2026-06-20 feat: added INA sensors and alerts reading, implemented INA get function and added guard for non supported PDO contracts for the primary USB-C
2026-06-20 fix: minor changes
2026-06-20 feat: added TPS25750 config file & bin
2026-06-21 feat: added charge management documentation
2026-06-21 fix: resolved pagination bugs
2026-06-22 fix: resolved some pagination bugs
2026-06-22 feat: remade the PCB & minor schematic fixes
2026-06-22 feat: gitignore
2026-06-24 feat: completed Sensing board
2026-06-24 feat: final version before prod
2026-06-24 feat: prod files
2026-06-26 feat: added other ALERT_STATUS register's bits handling and modified lower-bound voltage for STPD01 setup + some fixes
2026-06-28 fix: updated pin names & added missing pins
2026-06-28 fix: updated cubeMX generated code
2026-06-28 feat: license
